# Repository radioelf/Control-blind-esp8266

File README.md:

# Control-blind-esp8266 (Kicad Version: 5.99.0-unknown nightly)
PCB + software para el control de persianas motorizadas

PCB + software for the control of motorized blinds

Creative Commons License Disclaimer

UNLESS OTHERWISE MUTUALLY AGREED TO BY THE PARTIES IN WRITING, LICENSOR OFFERS THE WORK AS-IS AND MAKES NO REPRESENTATIONS OR WARRANTIES OF ANY KIND CONCERNING THE WORK, EXPRESS, IMPLIED, STATUTORY OR OTHERWISE, INCLUDING, WITHOUT LIMITATION, WARRANTIES OF TITLE, MERCHANTIBILITY, FITNESS FOR A PARTICULAR PURPOSE, NONINFRINGEMENT, OR THE ABSENCE OF LATENT OR OTHER DEFECTS, ACCURACY, OR THE PRESENCE OF ABSENCE OF ERRORS, WHETHER OR NOT DISCOVERABLE. SOME JURISDICTIONS DO NOT ALLOW THE EXCLUSION OF IMPLIED WARRANTIES, SO SUCH EXCLUSION MAY NOT APPLY TO YOU. EXCEPT TO THE EXTENT REQUIRED BY APPLICABLE LAW, IN NO EVENT WILL LICENSOR BE LIABLE TO YOU ON ANY LEGAL THEORY FOR ANY SPECIAL, INCIDENTAL, CONSEQUENTIAL, PUNITIVE OR EXEMPLARY DAMAGES ARISING OUT OF THIS LICENSE OR THE USE OF THE WORK, EVEN IF LICENSOR HAS BEEN ADVISED OF THE POSSIBILITY OF SUCH DAMAGES.

http://creativecommons.org/licenses/by-sa/3.0/

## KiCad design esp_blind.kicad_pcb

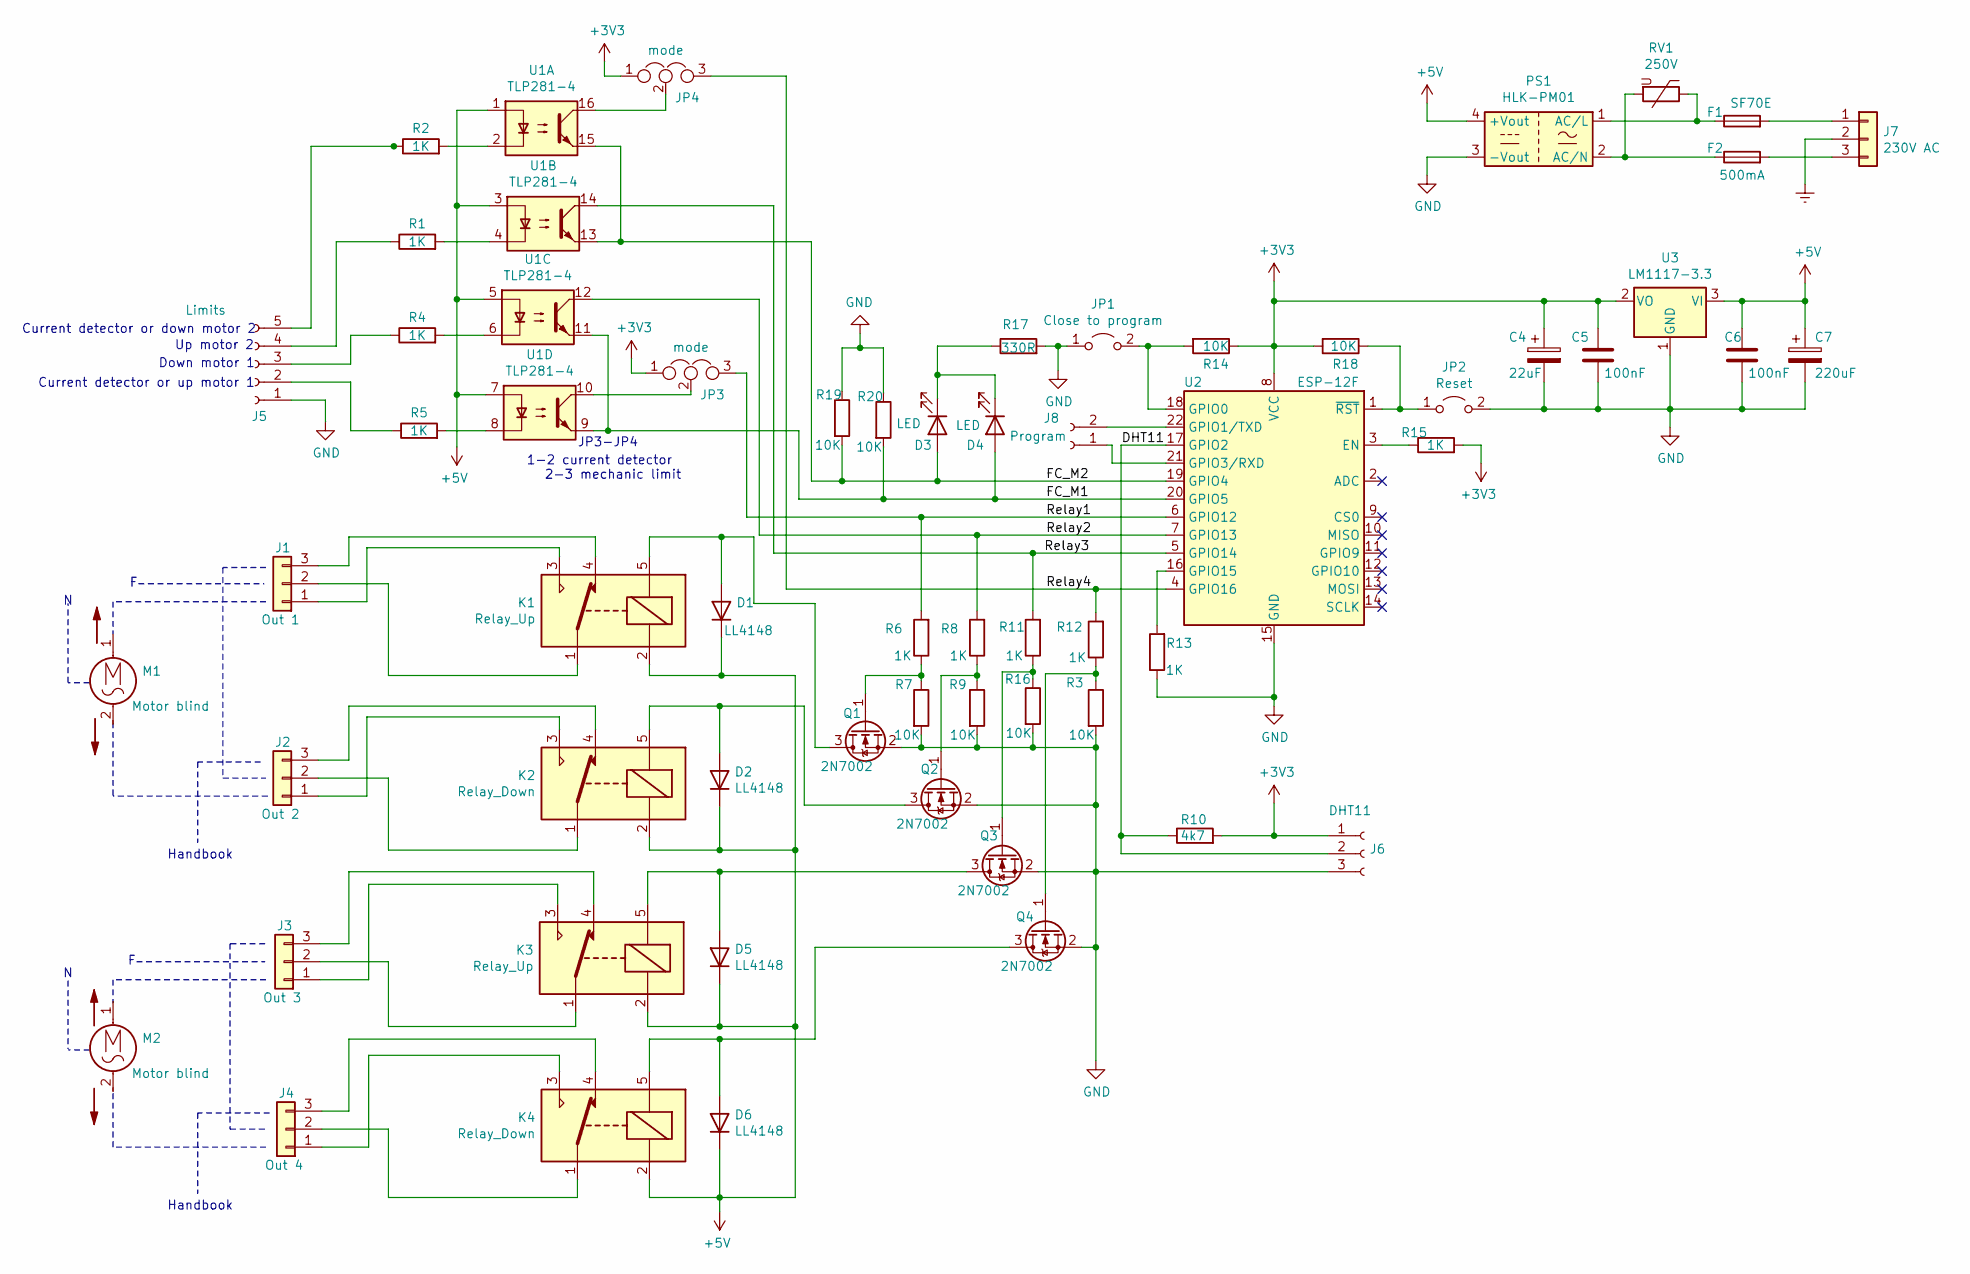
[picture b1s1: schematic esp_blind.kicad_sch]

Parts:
C4: 22uF; CP_Elec_4x5.8
C5, C6: 100nF; L_0805_2012Metric_Pad1.15x1.40mm_HandSolder
C7: 220uF; CP_Elec_5x4.4
D1, D2, D5, D6: LL4148; D_MiniMELF
D3, D4: LED; LED_0805_2012Metric
F1: SF70E; R_Axial_DIN0411_L9.9mm_D3.6mm_P7.62mm_Vertical
F2: 500mA; R_Axial_DIN0207_L6.3mm_D2.5mm_P7.62mm_Horizontal
J1: Out 1; JST_NV_B03P-NV_1x03_P5.00mm_Vertical
J2: Out 2; JST_NV_B03P-NV_1x03_P5.00mm_Vertical
J3: Out 3; JST_NV_B03P-NV_1x03_P5.00mm_Vertical
J4: Out 4; JST_NV_B03P-NV_1x03_P5.00mm_Vertical
J5: Limits; PinHeader_1x05_P2.54mm_Vertical
J6: DHT11; PinHeader_1x03_P2.54mm_Vertical
J7: 230V AC; JST_NV_B03P-NV_1x03_P5.00mm_Vertical
J8: Program; PinHeader_1x02_P2.54mm_Vertical
JP1: Close to program; PinHeader_1x02_P2.54mm_Vertical
JP2: Reset; PinHeader_1x02_P2.54mm_Vertical
JP3, JP4: mode; SolderJumper-3_P1.3mm_Open_Pad1.0x1.5mm
K1, K3: Relay_Up; Relay_SPDT_SANYOU_SRD_Series_Form_C
K2, K4: Relay_Down; Relay_SPDT_SANYOU_SRD_Series_Form_C
M1, M2: Motor blind
PS1: HLK-PM01; Converter_ACDC_HiLink_HLK-PMxx
Q1, Q2, Q3, Q4: 2N7002; SOT-23
R1, R2, R4, R5, R6, R8, R11, R12, R13, R15: 1K; R_0805_2012Metric
R3, R7, R9, R14, R16, R18, R19, R20: 10K; R_0805_2012Metric
R10: 4k7; R_0805_2012Metric
R17: 330R; R_0805_2012Metric
RV1: 250V; RV_Disc_D12mm_W3.9mm_P7.5mm
U1: TLP281-4; SOIC-16_4.55x10.3mm_P1.27mm
U2: ESP-12F; ESP-12E
U3: LM1117-3.3; SOT-223-3_TabPin2

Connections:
+3V3: C4.1, C5.2, J6.1, JP3.1, JP4.1, R10.2, R14.1, R15.2, R18.2, U2.8 (VCC), U3.2 (VO)
+5V: C6.2, C7.1, D1.1 (K), D2.1 (K), D5.1 (K), D6.1 (K), K1.2, K2.2, K3.2, K4.2, PS1.4 (+Vout), U1.1, U1.3, U1.5, U1.7, U3.3 (VI)
/DHT11: J6.2, R10.1, U2.17 (GPIO2)
/FC_M1: D4.2 (A), R20.2, U1.9, U1.11, U2.20 (GPIO5)
/FC_M2: D3.2 (A), R19.2, U1.13, U1.15, U2.19 (GPIO4)
/Relay1: JP3.3, R6.2, U2.6 (GPIO12)
/Relay2: R8.2, U1.12, U2.7 (GPIO13)
/Relay3: R11.2, U1.14, U2.5 (GPIO14)
/Relay4: JP4.3, R12.2, U2.4 (GPIO16)
Earth: J7.2
GND: C4.2, C5.1, C6.1, C7.2, J5.1, J6.3, JP1.1 (A), JP2.2 (B), PS1.3 (-Vout), Q1.2 (S), Q2.2 (S), Q3.2 (S), Q4.2 (S), R3.2, R7.2, R9.2, R13.1, R16.2, R17.2, R19.1, R20.1, U2.15 (GND), U3.1 (GND)
unnamed: D1.2 (A), K1.5, Q1.3 (D)
unnamed: D2.2 (A), K2.5, Q2.3 (D)
unnamed: D3.1 (K), D4.1 (K), R17.1
unnamed: D5.2 (A), K3.5, Q3.3 (D)
unnamed: D6.2 (A), K4.5, Q4.3 (D)
unnamed: F1.1, PS1.1 (AC/L), RV1.1
unnamed: F1.2, J7.1
unnamed: F2.1, PS1.2 (AC/N), RV1.2
unnamed: F2.2, J7.3
unnamed: J1.1, K1.3
unnamed: J1.2, K1.1
unnamed: J1.3, K1.4
unnamed: J2.1, K2.3
unnamed: J2.2, K2.1
unnamed: J2.3, K2.4
unnamed: J3.1, K3.3
unnamed: J3.2, K3.1
unnamed: J3.3, K3.4
unnamed: J4.1, K4.3
unnamed: J4.2, K4.1
unnamed: J4.3, K4.4
unnamed: J5.2, R5.1
unnamed: J5.3, R4.1
unnamed: J5.4, R1.1
unnamed: J5.5, R2.1
unnamed: J8.1, U2.21 (GPIO3/RXD)
unnamed: J8.2, U2.22 (GPIO1/TXD)
unnamed: JP1.2 (B), R14.2, U2.18 (GPIO0)
unnamed: JP2.1 (A), R18.1, U2.1 (~RST)
unnamed: JP3.2, U1.10
unnamed: JP4.2, U1.16
unnamed: Q1.1 (G), R6.1, R7.1
unnamed: Q2.1 (G), R8.1, R9.1
unnamed: Q3.1 (G), R11.1, R16.1
unnamed: Q4.1 (G), R3.1, R12.1
unnamed: R1.2, U1.4
unnamed: R2.2, U1.2
unnamed: R4.2, U1.6
unnamed: R5.2, U1.8
unnamed: R13.2, U2.16 (GPIO15)
unnamed: R15.1, U2.3 (EN)

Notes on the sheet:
Current detector or down motor 2
Current detector or up motor 1
Down motor 1
Up motor 2
Handbook
JP3-JP4
1-2 current detector
2-3 mechanic limit

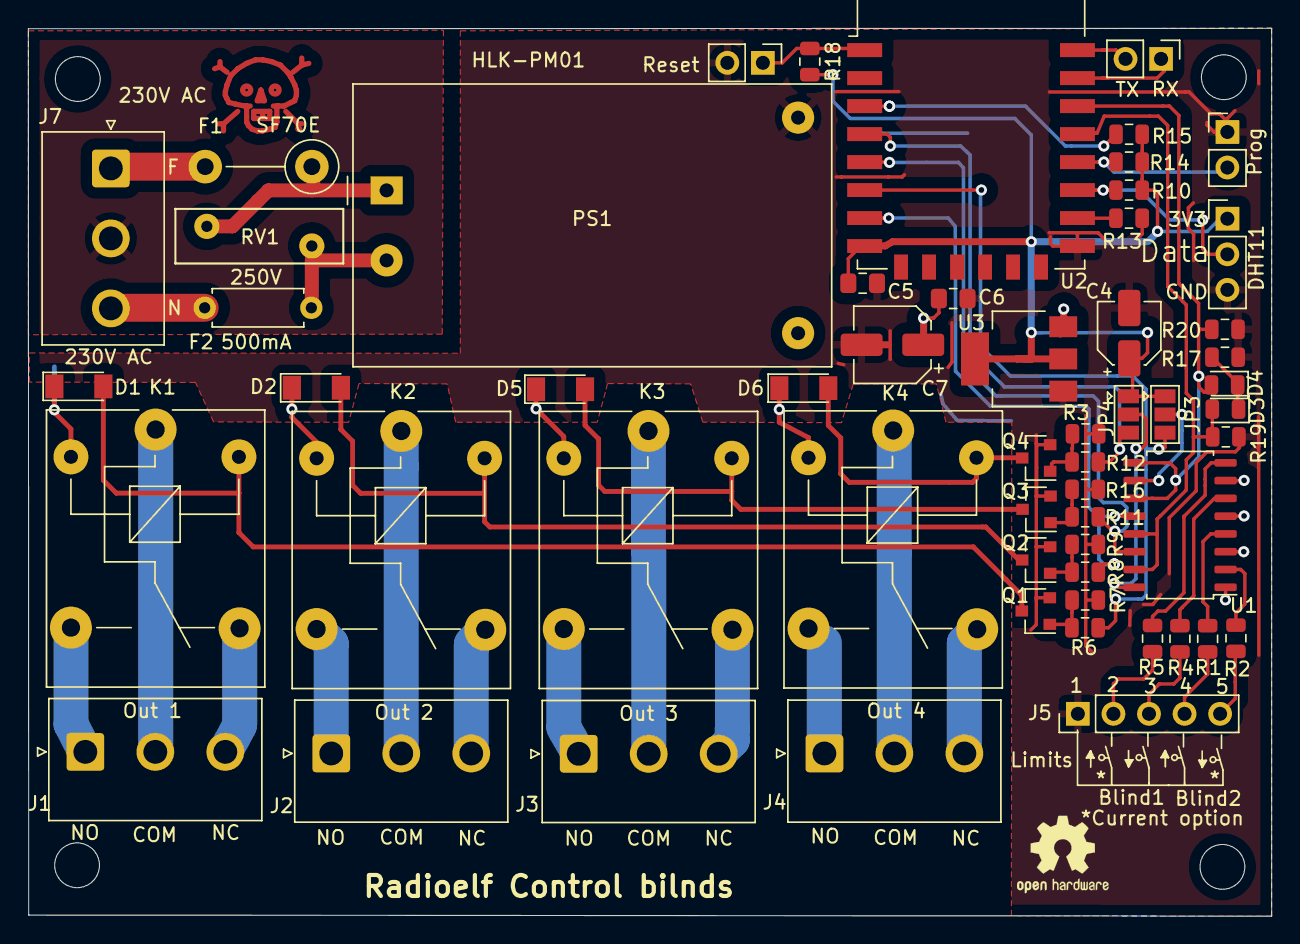
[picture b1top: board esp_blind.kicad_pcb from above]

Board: 2 copper layers, 88.8 x 63.4 mm, 58 parts (0 on the bottom side), 51 nets.

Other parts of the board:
230V AC: Danger; Symbol_Danger_CopperTop_Small

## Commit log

2021-06-02 Create software
2021-06-02 Update software
